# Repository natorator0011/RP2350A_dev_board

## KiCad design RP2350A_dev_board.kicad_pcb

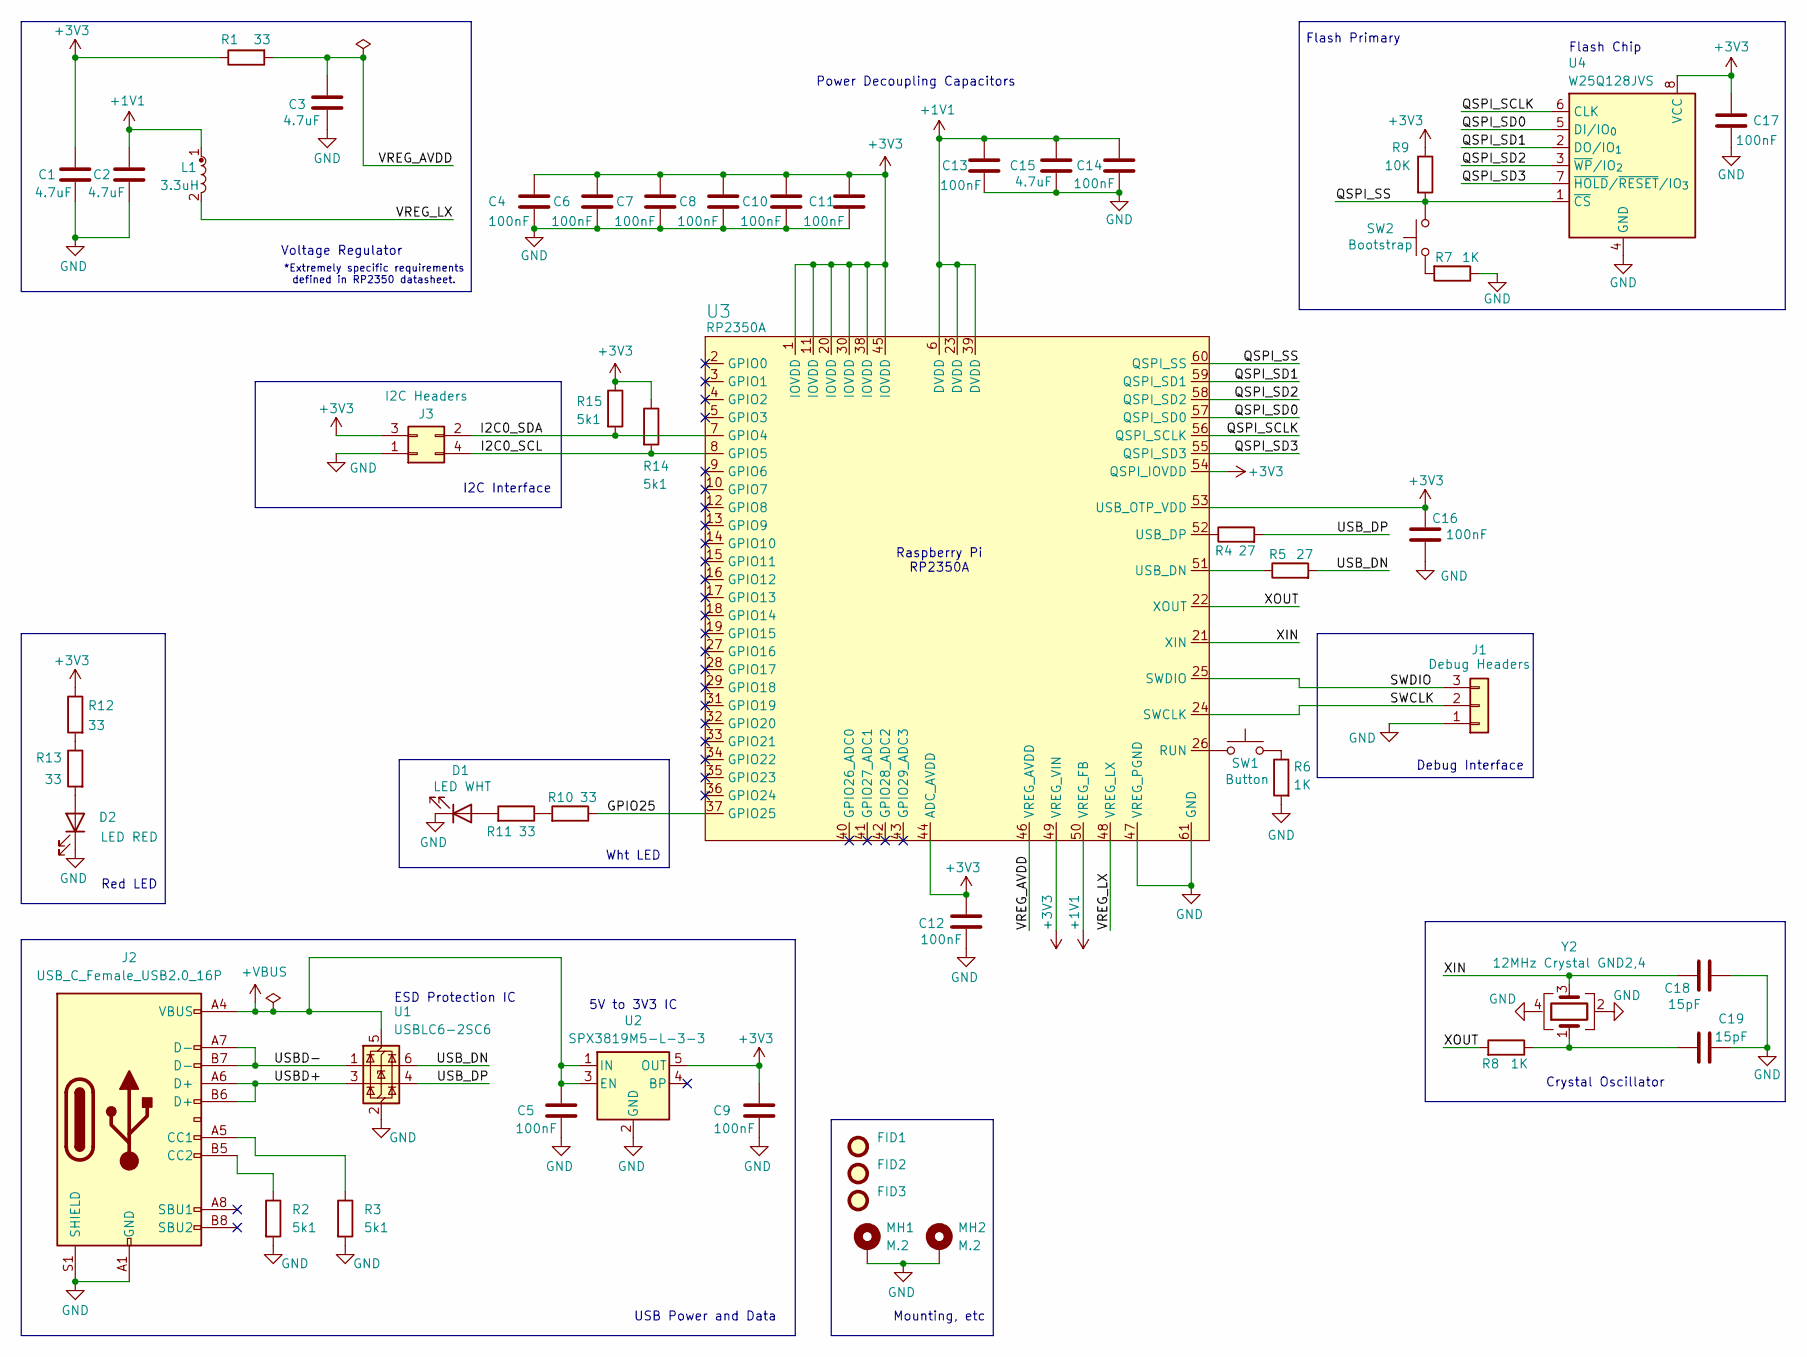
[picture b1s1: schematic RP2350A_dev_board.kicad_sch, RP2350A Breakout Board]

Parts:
C1, C2, C3, C15: 4.7uF; C_0603_1608Metric; Manufacturer Part Number CL10A475KO8NNNC; LCSC Part Number C19666
C4, C5, C6, C7, C8, C9, C10, C11, C12, C13, C14, C16, C17: 100nF; C_0603_1608Metric; Manufacturer Part Number CC0603KRX7R9BB104; LCSC Part Number C14663
C18, C19: 15pF; C_0603_1608Metric; Manufacturer Part Number CL10C150JB8NNNC; LCSC Part Number C1644
D1: LED WHT; LED_0603_1608Metric; Manufacturer Part Number KT-0603W; LCSC Part Number C2290
D2: LED RED; LED_0603_1608Metric; Manufacturer Part Number KT-0603R; LCSC Part Number C2286
FID1, FID2, FID3: Fiducial_1mm_Mask2mm
J1: Debug Headers; PinHeader_1x03_P2.54mm_Vertical
J2: USB_C_Female_USB2.0_16P; USB_C_Receptacle_GCT_USB4105-xx-A_16P_TopMnt_Horizontal; Manufacturer Part Number USB4105-GF-A-060; LCSC Part Number C3025063
J3: I2C Headers; PinHeader_2x02_P2.54mm_Vertical
L1: 3.3uH; AOTA-B201610S3R3-101-T_custom; Manufacturer Part Number AOTA-B201610S3R3-101-T; LCSC Part Number C42411119
MH1, MH2: M.2; MountingHole_2.2mm_M2_Pad_Via
R1, R10, R11, R12, R13: 33; R_0603_1608Metric; Manufacturer Part Number 0603WAF330JT5E; LCSC Part Number C23140
R2, R3, R14, R15: 5k1; R_0603_1608Metric; Manufacturer Part Number 0603WAF5101T5E; LCSC Part Number C23186
R4, R5: 27; R_0603_1608Metric; Manufacturer Part Number RCT0327RJLF; LCSC Part Number C177401
R6, R7, R8: 1K; R_0603_1608Metric; Manufacturer Part Number 0603WAF1001T5E; LCSC Part Number C21190
R9: 10K; R_0603_1608Metric; Manufacturer Part Number 0603WAF1002T5E; LCSC Part Number C25804
SW1: Button; SW_SPST_TS-1088-xR020; Manufacturer Part Number TS-1088-AR02016; LCSC Part Number C720477
SW2: Bootstrap; SW_SPST_TS-1088-xR020; Manufacturer Part Number TS-1088-AR02016; LCSC Part Number C720477
U1: USBLC6-2SC6; SOT-23-6; Manufacturer Part Number USBLC6-2SC6; LCSC Part Number C7519
U2: SPX3819M5-L-3-3; SOT-23-5; Manufacturer Part Number SPX3819M5-L-3-3; LCSC Part Number C20617301
U3: RP2350A; QFN-60-1EP_7x7mm_P0.4mm_EP3.4x3.4mm; Manufacturer Part Number RP2350A; LCSC Part Number C42411118
U4: W25Q128JVS; SOIC-8_5.3x5.3mm_P1.27mm; Manufacturer Part Number W25Q128JVSIQ; LCSC Part Number C97521
Y2: 12MHz Crystal GND2,4; ABM8-272-T3; Manufacturer Part Number ABM8-272-T3; LCSC Part Number C20625731

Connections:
+1V1: C2.1, C13.1, C14.1, C15.1, L1.1, U3.6 (DVDD), U3.23 (DVDD), U3.39 (DVDD), U3.50 (VREG_FB)
+3V3: C1.2, C4.1, C6.1, C7.1, C8.1, C9.1, C10.1, C11.1, C12.1, C16.2, C17.1, J3.3, R1.1, R9.1, R12.1, R14.1, R15.1, U2.5 (OUT), U3.1 (IOVDD), U3.11 (IOVDD), U3.20 (IOVDD), U3.30 (IOVDD), U3.38 (IOVDD), U3.44 (ADC_AVDD), U3.45 (IOVDD), U3.49 (VREG_VIN), U3.53 (USB_OTP_VDD), U3.54 (QSPI_IOVDD), U4.8 (VCC)
+VBUS: C5.1, J2.A4 (VBUS), J2.A9 (VBUS), J2.B4 (VBUS), J2.B9 (VBUS), U1.5 (VBUS), U2.1 (IN), U2.3 (EN)
/GPIO25: R10.1, U3.37 (GPIO25)
/I2C0_SCL: J3.4 (Pin_2), R14.2, U3.8 (GPIO5)
/I2C0_SDA: J3.2 (Pin_4), R15.2, U3.7 (GPIO4)
/QSPI_SCLK: U3.56 (QSPI_SCLK), U4.6 (CLK)
/QSPI_SD0: U3.57 (QSPI_SD0), U4.5 (DI/IO_{0})
/QSPI_SD1: U3.59 (QSPI_SD1), U4.2 (DO/IO_{1})
/QSPI_SD2: U3.58 (QSPI_SD2), U4.3 (~WP/IO_{2})
/QSPI_SD3: U3.55 (QSPI_SD3), U4.7 (~HOLD/~RESET/IO_{3})
/QSPI_SS: R9.2, SW2.2, U3.60 (QSPI_SS), U4.1 (~CS)
/SWCLK: J1.2, U3.24 (SWCLK)
/SWDIO: J1.3, U3.25 (SWDIO)
/USBD+: J2.A6 (D+), J2.B6 (D+), U1.3 (I/O2)
/USBD-: J2.A7 (D-), J2.B7 (D-), U1.1 (I/O1)
/USB_DN: R5.2, U1.6 (I/O1)
/USB_DP: R4.2, U1.4 (I/O2)
/VREG_AVDD: C3.2, R1.2, U3.46 (VREG_AVDD)
/VREG_LX: L1.2, U3.48 (VREG_LX)
/XIN: C18.2, U3.21 (XIN), Y2.3
/XOUT: R8.2, U3.22 (XOUT)
GND: C1.1, C2.2, C3.1, C4.2, C5.2, C6.2, C7.2, C8.2, C9.2, C10.2, C11.2, C12.2, C13.2, C14.2, C15.2, C16.1, C17.2, C18.1, C19.1, D1.1 (K), D2.1 (K), J1.1, J2.A1 (GND), J2.A12 (GND), J2.B1 (GND), J2.B12 (GND), J2.S1 (SHIELD), J3.1, MH1.1, MH2.1, R2.2, R3.2, R6.2, R7.1, U1.2 (GND), U2.2 (GND), U3.47 (VREG_PGND), U3.61 (GND), U4.4 (GND), Y2.2 (G), Y2.4 (G)
unnamed: C19.2, R8.1, Y2.1
unnamed: D1.2 (A), R11.2
unnamed: D2.2 (A), R13.2
unnamed: J2.A5 (CC1), R3.1
unnamed: J2.B5 (CC2), R2.1
unnamed: R6.1, SW1.2
unnamed: R7.2, SW2.1
unnamed: R10.2, R11.1
unnamed: R12.2, R13.1
unnamed: SW1.1, U3.26 (RUN)
unnamed: R5.1, U3.51 (USB_DN)
unnamed: R4.1, U3.52 (USB_DP)

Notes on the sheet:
5V to 3V3 IC
I2C Interface
Debug Interface
Raspberry Pi RP2350A
Mounting, etc
*Extremely specific requirements defined in RP2350 datasheet.
ESD Protection IC
Power Decoupling Capacitors
Flash Primary
Flash Chip
Red LED
USB Power and Data
Wht LED
Voltage Regulator
Crystal Oscillator

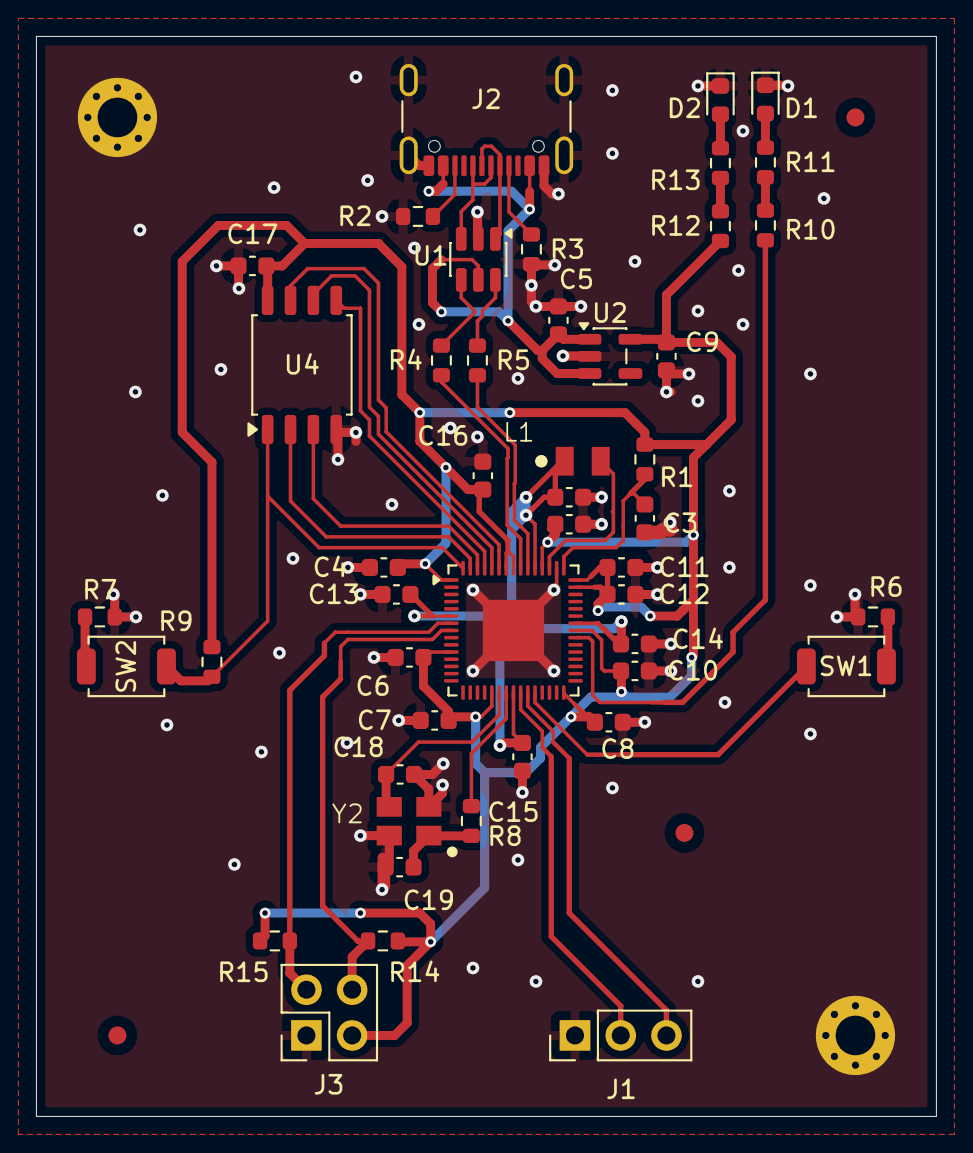
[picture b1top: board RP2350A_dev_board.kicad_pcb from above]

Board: 2 copper layers, 50.0 x 60.0 mm, 52 parts (0 on the bottom side), 35 nets.

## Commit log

2026-02-19 Added Red LED, Wht LED modules. Houskeeping.
2026-02-19 Removed tracking of cache file fp-info-cache
2026-02-19 Added I2C Interface, Debug Interface.
2026-02-20 Added and configured additional net classes. Began ERC fixes.
2026-02-20 Fixed all ERC issues.
2026-02-20 Reorganized for readability.
2026-02-20 Reorganized again.
2026-02-21 Began PCB Layout. reorganized DVDD decoupling capacitors for readability. Fixed L1 inductor footprint, Y2 Crystal footprint.
2026-02-21 Finished rough layout. Incorporated 5.1K pull-up resistors for I2C lines.
2026-02-21 Modified PCB layout, added GND plane on layer 2, began adding GND vias.
2026-02-22 Added vias to Voltage Regulator.
2026-02-25 Fixed via and ground plane interractions. Added +1V1 and +3V3 planes.
2026-02-26 Replaced +1V1 and +3V3 planes with wide routes. Routed all power. Finished all routing.
2026-02-27 Finished routing. Cleared ERC on schematic and layout.
2026-03-05 Final commit for time being, getting board printed and assembled was outside my price range. Unfortunately, oldering 0604 components is also outside my skill range. Project needs to be reorganized us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
